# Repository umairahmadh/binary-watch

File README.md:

# binary-watch
 
Based on https://www.instructables.com/The-Ultimate-Binary-Watch/

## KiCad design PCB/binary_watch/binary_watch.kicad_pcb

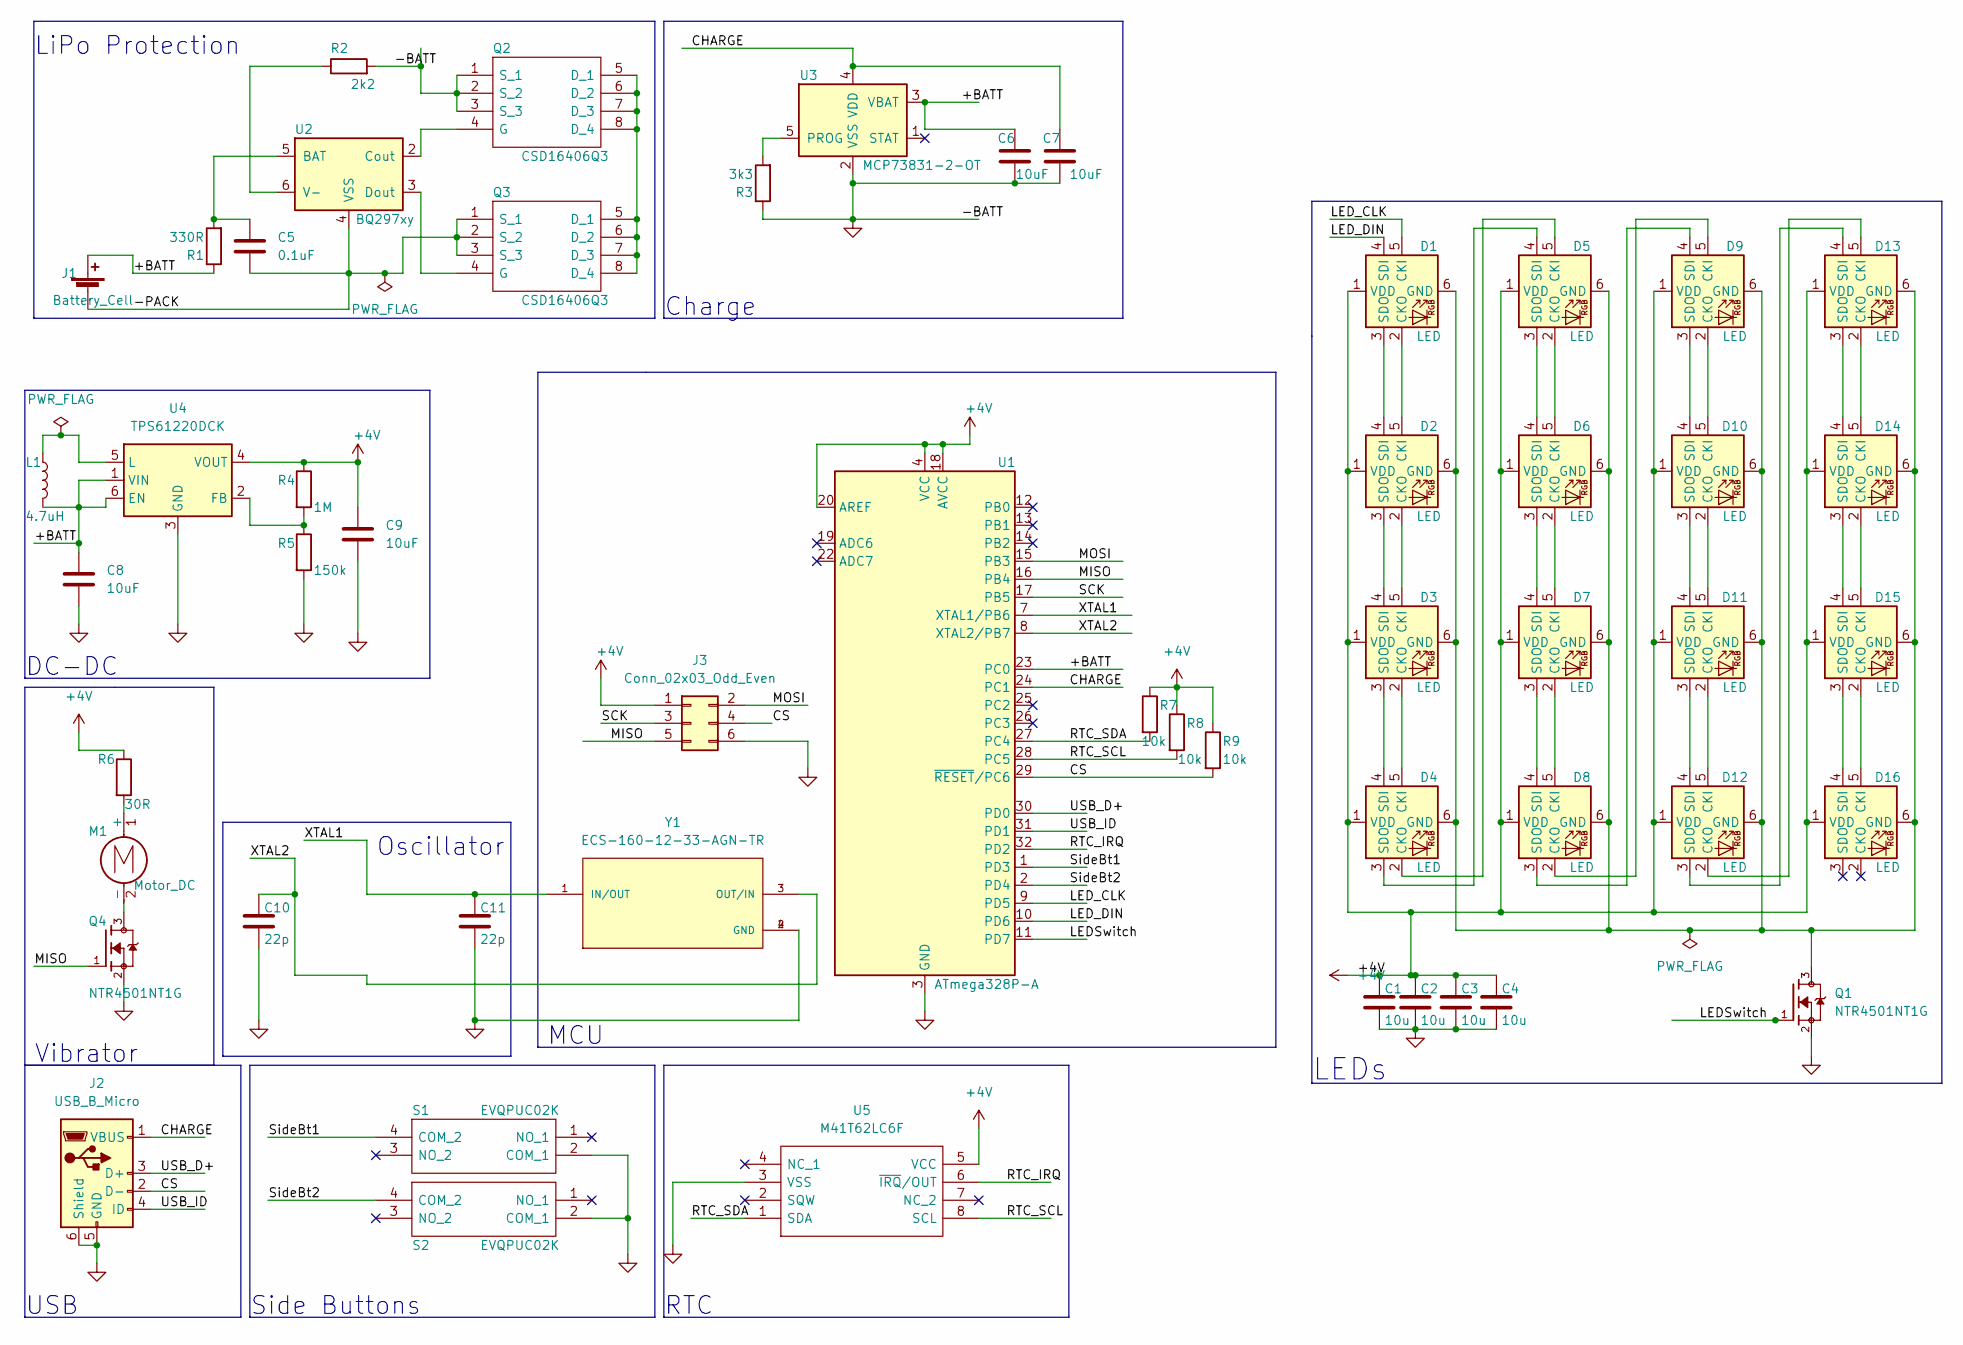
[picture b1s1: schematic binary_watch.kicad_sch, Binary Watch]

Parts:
C1, C2, C3, C4: 10u; C_0603_1608Metric
C5: 0.1uF; C_0603_1608Metric
C6, C7, C8, C9: 10uF; C_0603_1608Metric
C10, C11: 22p; C_0603_1608Metric
D1, D2, D3, D4, D5, D6, D7, D8, D9, D10, D11, D12, D13, D14, D15, D16: LED; LED-APA102-2020
J1: Battery_Cell; Battery_Panasonic_CR1025-VSK_Vertical_CircularHoles
J2: USB_B_Micro; USB_Micro-B_Amphenol_10118194_Horizontal
J3: Conn_02x03_Odd_Even; PinHeader_2x03_P2.54mm_Horizontal
L1: 4.7uH; L_Vishay_IHLP-1212
M1: Motor_DC; PinHeader_1x02_P2.54mm_Horizontal
Q1, Q4: NTR4501NT1G; SOT-23; PARTREV 15
Q2, Q3: CSD16406Q3; TRANS_CSD16406Q3; Manufacturer_Part_Number CSD16406Q3; Mouser Part Number 595-CSD16406Q3
R1: 330R; R_0603_1608Metric
R2: 2k2; R_0603_1608Metric
R3: 3k3; R_0603_1608Metric
R4: 1M; R_0603_1608Metric
R5: 150k; R_0603_1608Metric
R6: 30R; R_0603_1608Metric
R7, R8, R9: 10k; R_0603_1608Metric
S1, S2: EVQPUC02K; Manufacturer_Part_Number EVQPUC02K
U1: ATmega328P-A; TQFP-32_7x7mm_P0.8mm
U2: BQ297xy; WSON-6_1.5x1.5mm_P0.5mm
U3: MCP73831-2-OT; SOT-23-5
U4: TPS61220DCK; Texas_R-PDSO-G6
U5: M41T62LC6F; Manufacturer_Part_Number M41T62LC6F; Mouser Part Number 511-M41T62LC6F
Y1: ECS-160-12-33-AGN-TR; XTAL_ECS-160-12-33-AGN-TR

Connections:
+4V: C1.1, C2.1, C3.1, C4.1, C9.1, D1.1 (VDD), D2.1 (VDD), D3.1 (VDD), D4.1 (VDD), D5.1 (VDD), D6.1 (VDD), D7.1 (VDD), D8.1 (VDD), D9.1 (VDD), D10.1 (VDD), D11.1 (VDD), D12.1 (VDD), D13.1 (VDD), D14.1 (VDD), D15.1 (VDD), D16.1 (VDD), J3.1, R4.1, R6.1, R7.1, R8.1, R9.1, U1.4 (VCC), U1.6 (VCC), U1.18 (AVCC), U1.20 (AREF), U4.4 (VOUT), U5.5 (VCC)
/+BATT: C6.1, C8.1, J1.1 (+), L1.2, R1.1, U1.23 (PC0), U3.3 (VBAT), U4.1 (VIN), U4.6 (EN)
/-PACK: C5.2, J1.2 (-), Q3.1 (S_1), Q3.2 (S_2), Q3.3 (S_3), U2.4 (VSS)
/CHARGE: C7.1, J2.1 (VBUS), U1.24 (PC1), U3.4 (VDD)
/CS: J2.2 (D-), J3.4, R9.2, U1.29 (~RESET/PC6)
/LEDSwitch: Q1.1, U1.11 (PD7)
/LED_CLK: D1.5 (CKI), U1.9 (PD5)
/LED_DIN: D1.4 (SDI), U1.10 (PD6)
/MISO: J3.5, Q4.1, U1.16 (PB4)
/MOSI: J3.2, U1.15 (PB3)
/RTC_IRQ: U1.32 (PD2), U5.6 (~IRQ/OUT)
/RTC_SCL: R8.2, U1.28 (PC5), U5.8 (SCL)
/RTC_SDA: R7.2, U1.27 (PC4), U5.1 (SDA)
/SCK: J3.3, U1.17 (PB5)
/SideBt1: S1.4 (COM_2), U1.1 (PD3)
/SideBt2: S2.4 (COM_2), U1.2 (PD4)
/USB_D+: J2.3 (D+), U1.30 (PD0)
/USB_ID: J2.4 (ID), U1.31 (PD1)
/XTAL1: C11.1, U1.7 (XTAL1/PB6), Y1.1 (IN/OUT)
/XTAL2: C10.1, U1.8 (XTAL2/PB7), Y1.3 (OUT/IN)
GND: C1.2, C2.2, C3.2, C4.2, C6.2, C7.2, C8.2, C9.2, C10.2, C11.2, J2.5 (GND), J2.6 (Shield), J3.6, Q1.2, Q2.1 (S_1), Q2.2 (S_2), Q2.3 (S_3), Q4.2, R2.2, R3.1, R5.2, S1.2 (COM_1), S2.2 (COM_1), U1.3 (GND), U1.5 (GND), U1.21 (GND), U3.2 (VSS), U4.3 (GND), U5.3 (VSS), Y1.2 (GND), Y1.4 (GND)
unnamed: C5.1, R1.2, U2.5 (BAT)
unnamed: D1.2 (CKO), D2.5 (CKI)
unnamed: D1.3 (SDO), D2.4 (SDI)
unnamed: D1.6 (GND), D2.6 (GND), D3.6 (GND), D4.6 (GND), D5.6 (GND), D6.6 (GND), D7.6 (GND), D8.6 (GND), D9.6 (GND), D10.6 (GND), D11.6 (GND), D12.6 (GND), D13.6 (GND), D14.6 (GND), D15.6 (GND), D16.6 (GND), Q1.3
unnamed: D2.2 (CKO), D3.5 (CKI)
unnamed: D2.3 (SDO), D3.4 (SDI)
unnamed: D3.2 (CKO), D4.5 (CKI)
unnamed: D3.3 (SDO), D4.4 (SDI)
unnamed: D4.2 (CKO), D5.5 (CKI)
unnamed: D4.3 (SDO), D5.4 (SDI)
unnamed: D5.2 (CKO), D6.5 (CKI)
unnamed: D5.3 (SDO), D6.4 (SDI)
unnamed: D6.2 (CKO), D7.5 (CKI)
unnamed: D6.3 (SDO), D7.4 (SDI)
unnamed: D7.2 (CKO), D8.5 (CKI)
unnamed: D7.3 (SDO), D8.4 (SDI)
unnamed: D8.2 (CKO), D9.5 (CKI)
unnamed: D8.3 (SDO), D9.4 (SDI)
unnamed: D10.2 (CKO), D11.5 (CKI)
unnamed: D10.3 (SDO), D11.4 (SDI)
unnamed: D9.3 (SDO), D10.4 (SDI)
unnamed: D9.2 (CKO), D10.5 (CKI)
unnamed: D11.2 (CKO), D12.5 (CKI)
unnamed: D11.3 (SDO), D12.4 (SDI)
unnamed: D12.2 (CKO), D13.5 (CKI)
unnamed: D12.3 (SDO), D13.4 (SDI)
unnamed: D13.2 (CKO), D14.5 (CKI)
unnamed: D13.3 (SDO), D14.4 (SDI)
unnamed: D14.2 (CKO), D15.5 (CKI)
unnamed: D14.3 (SDO), D15.4 (SDI)
unnamed: D15.2 (CKO), D16.5 (CKI)
unnamed: D15.3 (SDO), D16.4 (SDI)
unnamed: L1.1, U4.5 (L)
unnamed: M1.1 (+), R6.2
unnamed: M1.2 (-), Q4.3
unnamed: Q2.4 (G), U2.2 (Cout)
unnamed: Q2.5 (D_1), Q2.6 (D_2), Q2.7 (D_3), Q2.8 (D_4), Q3.5 (D_1), Q3.6 (D_2), Q3.7 (D_3), Q3.8 (D_4)
unnamed: Q3.4 (G), U2.3 (Dout)
unnamed: R2.1, U2.6 (V-)
unnamed: R3.2, U3.5 (PROG)
unnamed: R4.2, R5.1, U4.2 (FB)

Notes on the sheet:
Vibrator
Oscillator
USB
RTC
LEDs
Charge
DC-DC
Side Buttons
MCU
LiPo Protection

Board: 2 copper layers, 53 parts (37 on the bottom side), 62 nets, no tracks yet.

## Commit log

2022-11-25 added files
2022-11-25 renamed src to pcb
2022-11-25 updated readme with instructable link
2022-12-04 Added more sections on the schematics, added library files.
2022-12-05 Completed Schematics
2022-12-31 component placement done
2024-06-29 add eagle files
2024-08-11 v0.5 finalised and ordered from JLC today
